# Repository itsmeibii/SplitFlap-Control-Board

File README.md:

# SplitFlap Display Control Board

A Raspberry Pi 4 controller board for a split-flap display with HUB75 LED matrix panels. One USB-C PD cable powers the Pi, the split-flap motor drivers and the LED panels.

## Features
- **USB-C PD input:** an Adafruit HUSB238 breakout asks the charger for 20 V / 3 A (60 W)
- **12–20 V → 5 V buck converter:** TI TPS56A37, up to ~8 A. An EN/UVLO divider keeps it off until PD has negotiated, and its power-good goes to a Pi GPIO.
- **Pi protection:** a TPS259474 eFuse on the Pi's 5 V rail (5.83 V overvoltage cutoff, 3.5 A current limit, power-good to a GPIO)
- **Fused outputs:** 7.5 A for the HUB75 panels and 3 A for the split-flap modules (ATO blade fuses)
- **TVS protection:** SMAJ22A on VBUS and SMAJ6.0A on 5 V
- **Connectors:** HUB75 data header, split-flap (Chainlink) data bus, two config buttons and status LEDs

## Repo layout
| Path | Contents |
|---|---|
| `control board/ControlBoard/` | KiCad 10 project (schematic, PCB, custom symbols/footprints) |
| `control board/ControlBoard/fab/` | JLCPCB gerbers, assembly files, DigiKey BOM |
| `housing/` | Enclosure: CadQuery scripts, STEP and STL files |
| `pi/` | Raspberry Pi smoke test for the Chainlink driver |
| `hub_75_test/` | HUB75 LED panel test firmware (Arduino + ESP-IDF) |
| `docs/` | Schematic PDF and renders |

## Schematics

## PCB
| Top | Bottom |
|:---:|:---:|
|  |  |

## Enclosure

The split-flap mechanism and driver boards come from [scottbez1/splitflap](https://github.com/scottbez1/splitflap). This repo contains only the control board and enclosure I designed for it.

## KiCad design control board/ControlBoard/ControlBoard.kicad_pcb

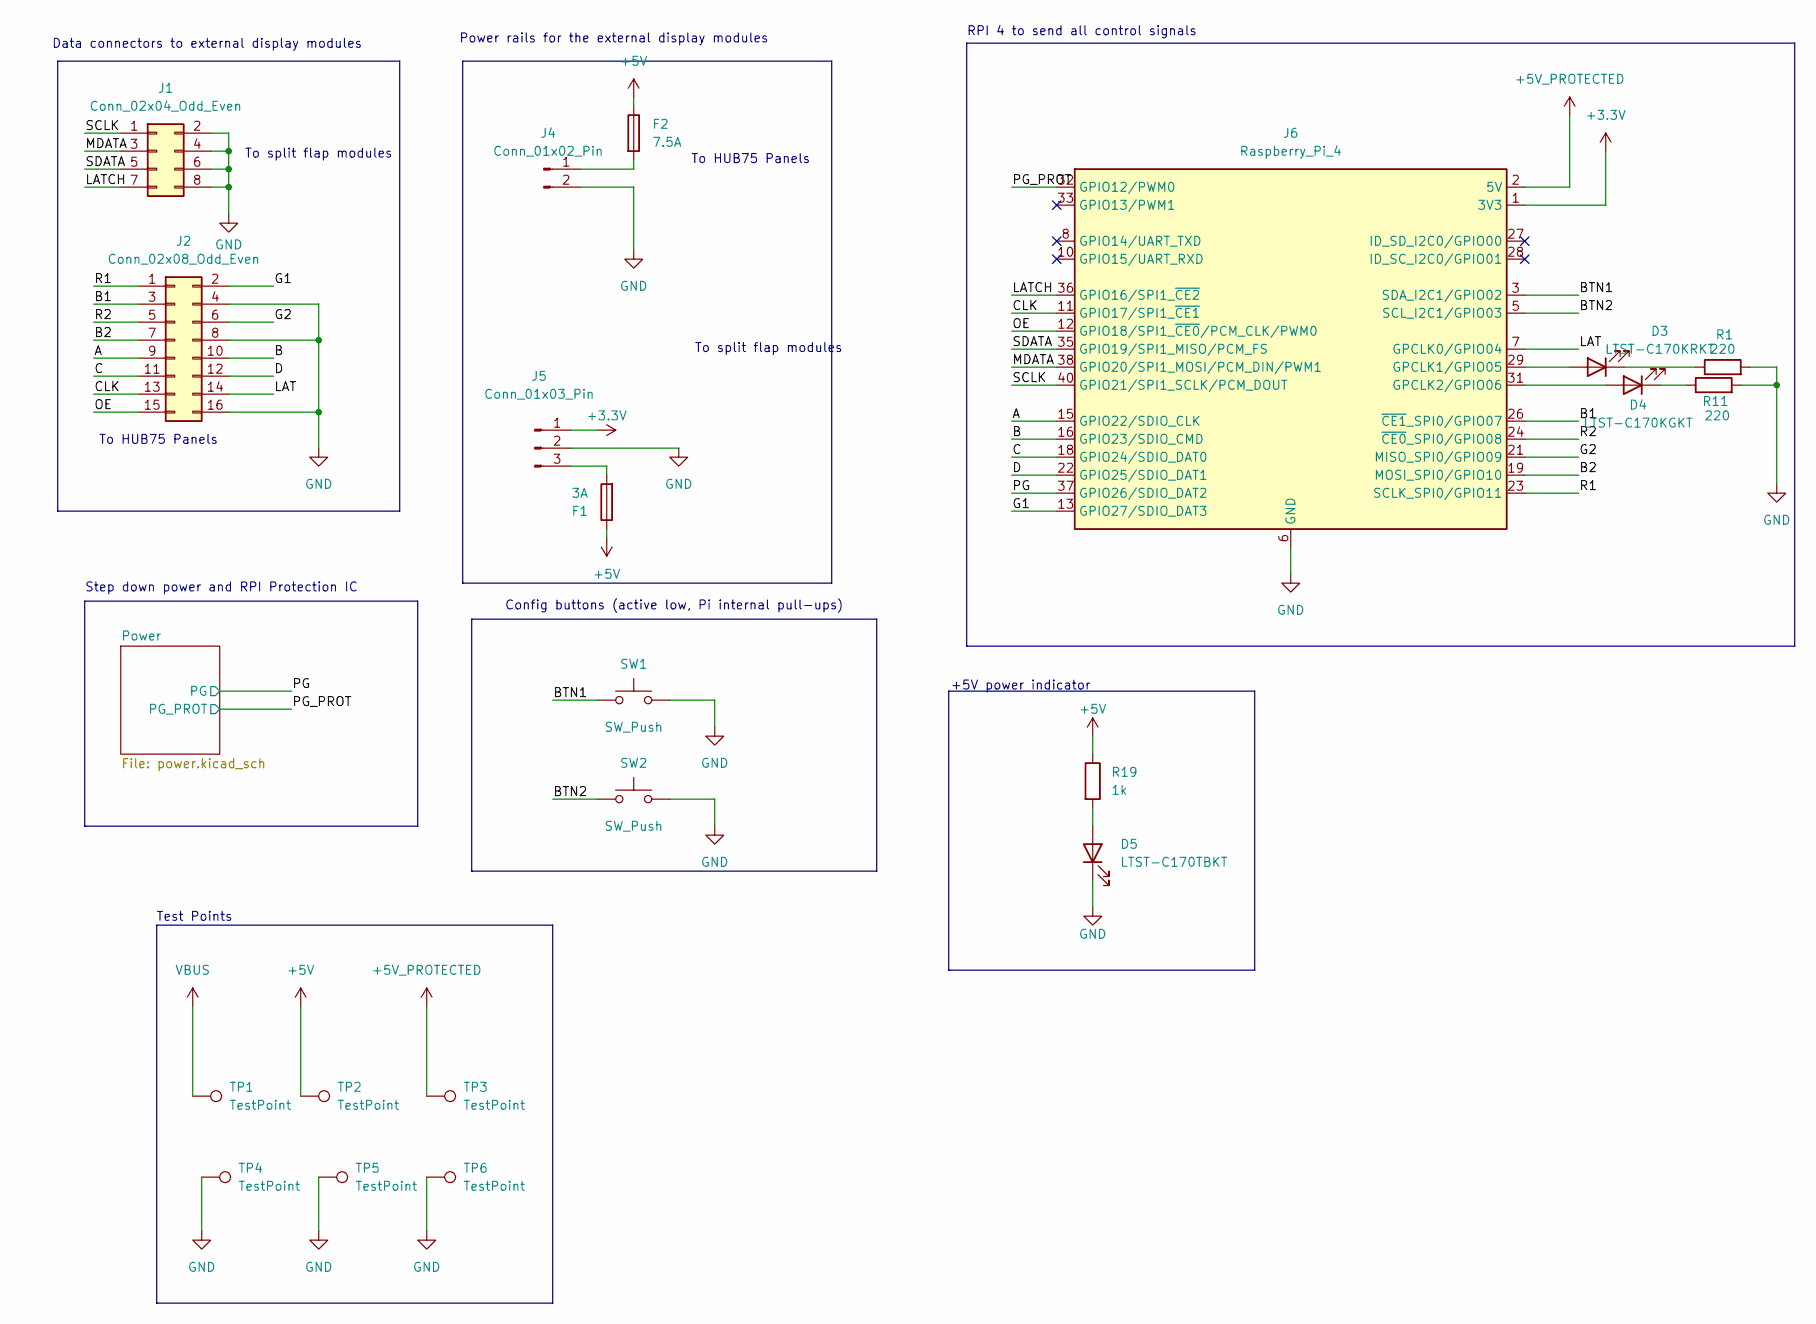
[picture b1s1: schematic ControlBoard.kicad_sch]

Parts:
D3: LTST-C170KRKT; LED_0805_2012Metric_Pad1.15x1.40mm_HandSolder; DigiKey Part # 160-1415-1-ND
D4: LTST-C170KGKT; LED_0805_2012Metric_Pad1.15x1.40mm_HandSolder; DigiKey Part # 160-1414-1-ND
D5: LTST-C170TBKT; LED_0805_2012Metric_Pad1.15x1.40mm_HandSolder; DigiKey Part # 160-1579-1-ND
F1: 3A; Fuseholder_Blade_Mini_Keystone_3568; MPN 3568; DigiKey Part # 36-3568-ND
F2: 7.5A; Fuseholder_Blade_Mini_Keystone_3568; MPN 3568; DigiKey Part # 36-3568-ND
J1: Conn_02x04_Odd_Even; IDC-Header_2x04_P2.54mm_Vertical; DigiKey Part # 732-5395-ND
J2: Conn_02x08_Odd_Even; IDC-Header_2x08_P2.54mm_Vertical; DigiKey Part # 732-2095-ND
J4: Conn_01x02_Pin; TerminalBlock_CUI_TB007-508-02_1x02_P5.08mm_Horizontal; DigiKey Part # 102-6191-ND
J5: Conn_01x03_Pin; TerminalBlock_CUI_TB007-508-03_1x03_P5.08mm_Horizontal; DigiKey Part # 102-6204-ND
J6: Raspberry_Pi_4; PinSocket_2x20_P2.54mm_Vertical; DigiKey Part # 2223-SSK04-FPH-254-B20-ND
R1, R11: 220; R_0805_2012Metric; DigiKey Part # 311-220CRCT-ND
R19: 1k; R_0805_2012Metric; DigiKey Part # 311-1.00KCRCT-ND
SW1, SW2: SW_Push; SW_PUSH_6mm; DigiKey Part # SW400-ND
TP1, TP2, TP3, TP4, TP5, TP6: TestPoint; TestPoint_Pad_D1.0mm

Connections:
+3.3V: J5.1, J6.1 (3V3), J6.17 (3V3); also elsewhere on the board
+5V: F1.1, F2.1, R19.1, TP2.1 (1_1); also elsewhere on the board
+5V_PROTECTED: J6.2 (5V), J6.4 (5V), TP3.1 (1_1); also elsewhere on the board
/A: J2.9, J6.15 (GPIO22/SDIO_CLK)
/B: J2.10, J6.16 (GPIO23/SDIO_CMD)
/B1: J2.3, J6.26 (~CE1_SPI0/GPIO07)
/B2: J2.7, J6.19 (MOSI_SPI0/GPIO10)
/BTN1: J6.3 (SDA_I2C1/GPIO02), SW1.1
/BTN2: J6.5 (SCL_I2C1/GPIO03), SW2.1
/C: J2.11, J6.18 (GPIO24/SDIO_DAT0)
/CLK: J2.13, J6.11 (GPIO17/SPI1_~CE1)
/D: J2.12, J6.22 (GPIO25/SDIO_DAT1)
/G1: J2.2, J6.13 (GPIO27/SDIO_DAT3)
/G2: J2.6, J6.21 (MISO_SPI0/GPIO09)
/LAT: J2.14, J6.7 (GPCLK0/GPIO04)
/LATCH: J1.7, J6.36 (GPIO16/SPI1_~CE2)
/MDATA: J1.3, J6.38 (GPIO20/SPI1_MOSI/PCM_DIN/PWM1)
/OE: J2.15, J6.12 (GPIO18/SPI1_~CE0/PCM_CLK/PWM0)
/PG: J6.37 (GPIO26/SDIO_DAT2); also elsewhere on the board
/PG_PROT: J6.32 (GPIO12/PWM0); also elsewhere on the board
/R1: J2.1, J6.23 (SCLK_SPI0/GPIO11)
/R2: J2.5, J6.24 (~CE0_SPI0/GPIO08)
/SCLK: J1.1, J6.40 (GPIO21/SPI1_SCLK/PCM_DOUT)
/SDATA: J1.5, J6.35 (GPIO19/SPI1_MISO/PCM_FS)
GND: D5.1 (K), J1.2, J1.4, J1.6, J1.8, J2.4, J2.8, J2.16, J4.2, J5.2, J6.6 (GND), J6.9 (GND), J6.14 (GND), J6.20 (GND), J6.25 (GND), J6.30 (GND), J6.34 (GND), J6.39 (GND), R1.2, R11.2, SW1.2, SW2.2, TP4.1 (1_1), TP5.1 (1_1), TP6.1 (1_1); also elsewhere on the board
unnamed: D3.2 (A), J6.29 (GPCLK1/GPIO05)
unnamed: D3.1 (K), R1.1
unnamed: D4.2 (A), J6.31 (GPCLK2/GPIO06)
unnamed: D4.1 (K), R11.1
unnamed: D5.2 (A), R19.2
unnamed: F2.2, J4.1
unnamed: F1.2, J5.3
VBUS: TP1.1 (1_1); also elsewhere on the board

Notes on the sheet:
+5V power indicator
RPI 4 to send all control signals
To split flap modules
Power rails for the external display modules
Step down power and RPI Protection IC
Config buttons (active low, Pi internal pull-ups)
Data connectors to external display modules
To HUB75 Panels
Test Points

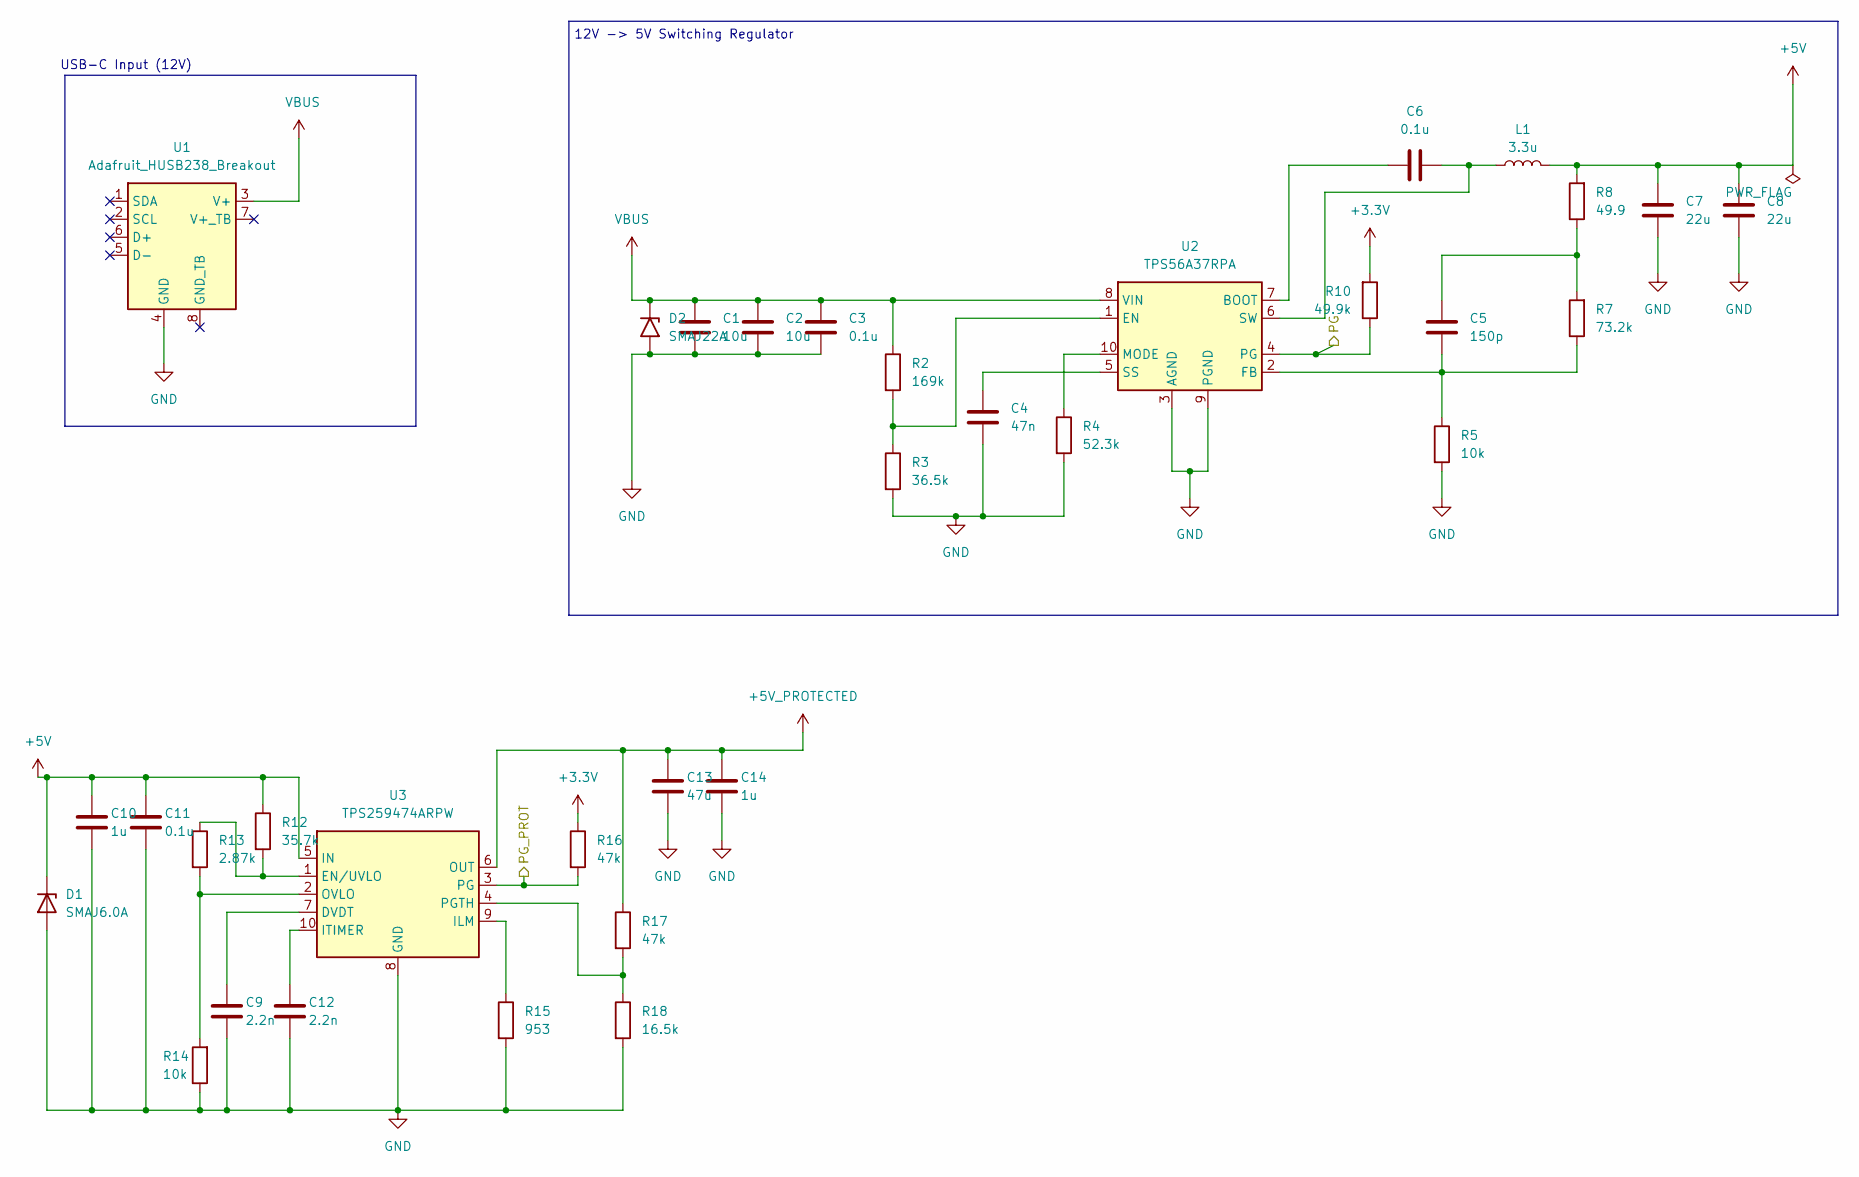
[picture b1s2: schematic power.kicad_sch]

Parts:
C1, C2: 10u; C_1206_3216Metric; DigiKey Part # 4713-GMC31X7R106K50NTCT-ND
C3, C6, C11: 0.1u; C_0805_2012Metric; DigiKey Part # 1276-1003-1-ND
C4: 47n; C_0805_2012Metric; DigiKey Part # 399-C0805C473K5RACTUCT-ND
C5: 150p; C_0805_2012Metric; DigiKey Part # 399-C0805C151J5GACTUCT-ND
C7, C8: 22u; C_1210_3225Metric; DigiKey Part # 490-3889-1-ND
C9, C12: 2.2n; C_0805_2012Metric; DigiKey Part # 1276-2993-1-ND
C10, C14: 1u; C_0805_2012Metric; DigiKey Part # 399-C0805C105K3RACTUCT-ND
C13: 47u; C_1210_3225Metric; DigiKey Part # 587-5479-1-ND
D1: SMAJ6.0A; D_SMA; DigiKey Part # SMAJ6.0ALFCT-ND
D2: SMAJ22A; D_SMA; DigiKey Part # SMAJ22ABCT-ND
L1: 3.3u; L_Wuerth_HCI-1050; DigiKey Part # 732-1169-1-ND
R2: 169k; R_0805_2012Metric; DigiKey Part # RMCF0805FT169KCT-ND
R3: 36.5k; R_0805_2012Metric; DigiKey Part # 311-36.5KCRCT-ND
R4: 52.3k; R_0805_2012Metric; DigiKey Part # 311-52.3KCRCT-ND
R5, R14: 10k; R_0805_2012Metric; DigiKey Part # 311-10.0KCRCT-ND
R7: 73.2k; R_0805_2012Metric; DigiKey Part # 311-73.2KCRCT-ND
R8: 49.9; R_0805_2012Metric; DigiKey Part # 311-49.9CRCT-ND
R10: 49.9k; R_0805_2012Metric; DigiKey Part # 311-49.9KCRCT-ND
R12: 35.7k; R_0805_2012Metric; DigiKey Part # 311-35.7KCRCT-ND
R13: 2.87k; R_0805_2012Metric; DigiKey Part # 311-2.87KCRCT-ND
R15: 953; R_0805_2012Metric; DigiKey Part # 311-953CRCT-ND
R16, R17: 47k; R_0805_2012Metric; DigiKey Part # 311-47.0KCRCT-ND
R18: 16.5k; R_0805_2012Metric; DigiKey Part # 311-16.5KCRCT-ND
U1: Adafruit_HUSB238_Breakout; DigiKey 1528-5807-ND
U2: TPS56A37RPA; Texas_RPA0010A_VQFN-HR-10_3x3mm_P0.5mm; DigiKey Part # 296-TPS56A37RPARCT-ND
U3: TPS259474ARPW; Texas_RPW0010A_VQFN-HR-10_2x2mm_P0.475mm; DigiKey Part # 296-TPS259474ARPWRCT-ND

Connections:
+3.3V: R10.2, R16.1; also elsewhere on the board
+5V: C7.2, C8.2, C10.1, C11.1, D1.1 (K), L1.2, R8.2, R12.1, U3.5 (IN); also elsewhere on the board
+5V_PROTECTED: C13.1, C14.1, R17.1, U3.6 (OUT); also elsewhere on the board
/PG: R10.1, U2.4 (PG); also elsewhere on the board
/PG_PROT: R16.2, U3.3 (PG); also elsewhere on the board
GND: C1.2, C2.2, C3.2, C4.2, C7.1, C8.1, C9.2, C10.2, C11.2, C12.2, C13.2, C14.2, D1.2 (A), D2.2 (A2), R3.2, R4.2, R5.2, R14.1, R15.2, R18.2, U1.4 (GND), U2.3 (AGND), U2.9 (PGND), U3.8 (GND); also elsewhere on the board
unnamed: C5.1, R7.2, R8.1
unnamed: C6.1, U2.7 (BOOT)
unnamed: R2.2, R3.1, U2.1 (EN)
unnamed: C5.2, R5.1, R7.1, U2.2 (FB)
unnamed: R4.1, U2.10 (MODE)
unnamed: C4.1, U2.5 (SS)
unnamed: C6.2, L1.1, U2.6 (SW)
unnamed: C9.1, U3.7 (DVDT)
unnamed: R12.2, R13.1, U3.1 (EN/UVLO)
unnamed: R15.1, U3.9 (ILM)
unnamed: C12.1, U3.10 (ITIMER)
unnamed: R13.2, R14.2, U3.2 (OVLO)
unnamed: R17.2, R18.1, U3.4 (PGTH)
VBUS: C1.1, C2.1, C3.1, D2.1 (A1), R2.1, U1.3 (V+), U2.8 (VIN); also elsewhere on the board

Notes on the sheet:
USB-C Input (12V)
12V -> 5V Switching Regulator

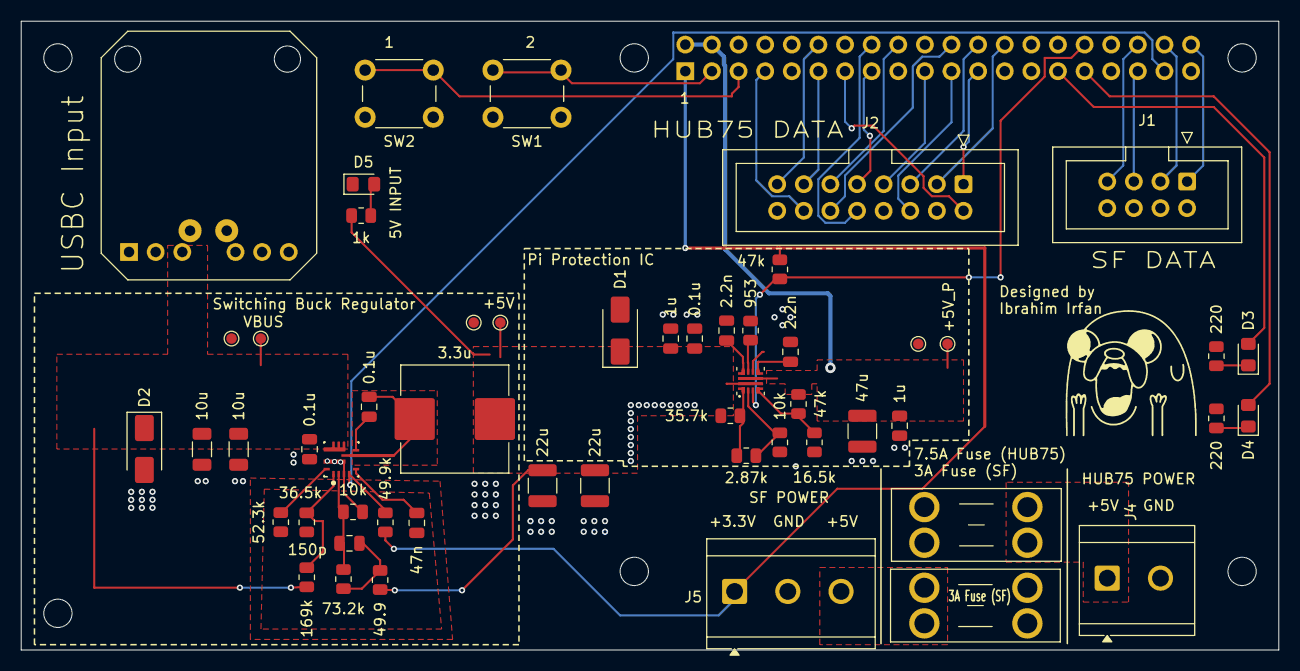
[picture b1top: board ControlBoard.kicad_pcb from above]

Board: 2 copper layers, 120.0 x 60.0 mm, 62 parts (1 on the bottom side), 46 nets.

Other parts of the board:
H1, H2, H3, H4, H5, H6: MountingHole_2.7mm_M2.5
LOGO1: Logo_Jake; Logo_Jake_Silkscreen_12mm

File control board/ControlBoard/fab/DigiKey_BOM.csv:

Qty per board,References,Value,Footprint,DigiKey Part #,Who solders
2,C1 C2,10u,C_1206_3216Metric,4713-GMC31X7R106K50NTCT-ND,You
3,C3 C6 C11,0.1u,C_0805_2012Metric,1276-1003-1-ND,You
1,C4,47n,C_0805_2012Metric,399-C0805C473K5RACTUCT-ND,You
1,C5,150p,C_0805_2012Metric,399-C0805C151J5GACTUCT-ND,You
2,C7 C8,22u,C_1210_3225Metric,490-3889-1-ND,You
2,C9 C12,2.2n,C_0805_2012Metric,1276-2993-1-ND,You
2,C10 C14,1u,C_0805_2012Metric,399-C0805C105K3RACTUCT-ND,You
1,C13,47u,C_1210_3225Metric,587-5479-1-ND,You
1,D1,SMAJ6.0A,D_SMA,SMAJ6.0ALFCT-ND,You
1,D2,SMAJ22A,D_SMA,SMAJ22ABCT-ND,You
1,D3,LTST-C170KRKT,LED_0805_2012Metric_Pad1.15x1.40mm_HandSolder,160-1415-1-ND,You
1,D4,LTST-C170KGKT,LED_0805_2012Metric_Pad1.15x1.40mm_HandSolder,160-1414-1-ND,You
1,D5,LTST-C170TBKT,LED_0805_2012Metric_Pad1.15x1.40mm_HandSolder,160-1579-1-ND,You
1,F1,3A,Fuseholder_Blade_Mini_Keystone_3568,36-3568-ND,You
1,F2,7.5A,Fuseholder_Blade_Mini_Keystone_3568,36-3568-ND,You
1,J1,Conn_02x04_Odd_Even,IDC-Header_2x04_P2.54mm_Vertical,732-5395-ND,You
1,J2,Conn_02x08_Odd_Even,IDC-Header_2x08_P2.54mm_Vertical,732-2095-ND,You
1,J4,Conn_01x02_Pin,TerminalBlock_CUI_TB007-508-02_1x02_P5.08mm_Horizontal,102-6203-ND,You
1,J5,Conn_01x03_Pin,TerminalBlock_CUI_TB007-508-03_1x03_P5.08mm_Horizontal,102-6204-ND,You
1,J6,Raspberry_Pi_4,PinSocket_2x20_P2.54mm_Vertical,2223-SSK04-FPH-254-B20-ND,You
1,L1,3.3u,L_Wuerth_HCI-1050,732-1169-1-ND,You
2,R1 R11,220,R_0805_2012Metric,311-220CRCT-ND,You
1,R2,169k,R_0805_2012Metric,RMCF0805FT169KCT-ND,You
1,R3,36.5k,R_0805_2012Metric,311-36.5KCRCT-ND,You
1,R4,52.3k,R_0805_2012Metric,311-52.3KCRCT-ND,You
2,R5 R14,10k,R_0805_2012Metric,311-10.0KCRCT-ND,You
1,R7,73.2k,R_0805_2012Metric,311-73.2KCRCT-ND,You
1,R8,49.9,R_0805_2012Metric,311-49.9CRCT-ND,You
1,R10,49.9k,R_0805_2012Metric,311-49.9KCRCT-ND,You
1,R12,35.7k,R_0805_2012Metric,311-35.7KCRCT-ND,You
1,R13,2.87k,R_0805_2012Metric,311-2.87KCRCT-ND,You
1,R15,953,R_0805_2012Metric,311-953CRCT-ND,You
2,R16 R17,47k,R_0805_2012Metric,311-47.0KCRCT-ND,You
1,R18,16.5k,R_0805_2012Metric,311-16.5KCRCT-ND,You
1,R19,1k,R_0805_2012Metric,311-1.00KCRCT-ND,You
2,SW1 SW2,SW_Push,SW_PUSH_6mm,SW400-ND,You
1,U1,Adafruit_HUSB238_Breakout,Adafruit_HUSB238_Breakout,1528-5807-ND,You
1,U2,TPS56A37RPA,Texas_RPA0010A_VQFN-HR-10_3x3mm_P0.5mm,296-TPS56A37RPARCT-ND,JLC (Global Sourcing - do not order)
1,U3,TPS259474ARPW,Texas_RPW0010A_VQFN-HR-10_2x2mm_P0.475mm,296-TPS259474ARPWRCT-ND,JLC (Global Sourcing - do not order)
6,"TP1,TP2,TP3,TP4,TP5,TP6",TestPoint,TestPoint_Pad_D1.0mm,(none - bare copper pad),Nothing to buy or solder

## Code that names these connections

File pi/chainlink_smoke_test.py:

#!/usr/bin/env python3
"""
Chainlink Driver smoke test for a Raspberry Pi 4 -- steps all six modules at once
so the peak motor-supply current can be measured.

Wiring (Chainlink "Input" 2x4 header -> Pi, BCM numbering):
    1 CLOCK      -> GPIO21 (pin 40)
    3 MOTOR      -> GPIO20 (pin 38)
    5 SENSOR_OUT -> GPIO19 (pin 35)
    7 LATCH      -> GPIO16 (pin 36)
    even pins    -> GND
    "Logic 3.3-5V" terminal -> Pi 3V3 (pin 1/17)   -- NOT 5V
    "Motor" terminal        -> bench supply V+, supply GND shared with the Pi

The bit layout mirrors firmware/src/spi_io_config.h (CHAINLINK, NUM_MODULES=6):
4 bytes are shifted out MSB-first, byte 0 first, so byte 3 lands in the
74HC595 nearest the input header. One LATCH line drives both the 595 RCLK
(rising edge = outputs update) and the 74HC165 SH/LD (low = parallel load,
high = shift), so after latching high we clock in one sensor byte.

Usage (needs python3-lgpio, preinstalled on Raspberry Pi OS Bookworm):
    python3 chainlink_smoke_test.py                 # step all 6 for 10 s
    python3 chainlink_smoke_test.py -t 30 -p 1800   # 30 s at 1.8 ms/step
    python3 chainlink_smoke_test.py --hold 5        # hold coils on 5 s (static worst case)
    python3 chainlink_smoke_test.py --modules 0 3   # only modules A and D
"""

import argparse
import signal
import sys
import time

import lgpio

PIN_CLK = 21
PIN_DATA = 20
PIN_SENSOR = 19
PIN_LATCH = 16

NUM_MODULES = 6
MOTOR_BYTES = 4

# (byte index, bit shift) of each module's 4 coil bits -- from initialize_modules()
MOTOR_SLOT = [(3, 0), (3, 4), (2, 0), (1, 4), (0, 0), (0, 4)]
# (byte index, bit mask) of each module's LED -- from chainlink_set_led()
LED_SLOT = [(2, 1 << 4), (2, 1 << 5), (2, 1 << 6), (1, 1 << 0), (1, 1 << 1), (1, 1 << 2)]

# Two-phase-on full stepping, same as the firmware (two coils energized per step)
STEP_PATTERN = [0b1100, 0b0110, 0b0011, 0b1001]

# Firmware starts at 10 ms/step and accelerates to ~1.6 ms/step
START_PERIOD_US = 10000
RAMP_STEPS = 72


class Chainlink:
    def __init__(self):
        self.h = lgpio.gpiochip_open(0)
        for pin in (PIN_CLK, PIN_DATA, PIN_LATCH):
            lgpio.gpio_claim_output(self.h, pin, 0)
        lgpio.gpio_claim_input(self.h, PIN_SENSOR)

    def io(self, motor_bytes):
        """Shift out motor bytes, latch them, and read back one sensor byte."""
        h = self.h
        write = lgpio.gpio_write
        write(h, PIN_LATCH, 0)
        for byte in motor_bytes:
            for bit in range(7, -1, -1):
                write(h, PIN_DATA, (byte >> bit) & 1)
                write(h, PIN_CLK, 1)
                write(h, PIN_CLK, 0)
        # Rising edge: 595 outputs update, 165 freezes its inputs for shifting
        write(h, PIN_LATCH, 1)
        sensors = 0
        for _ in range(8):
            sensors = (sensors << 1) | lgpio.gpio_read(h, PIN_SENSOR)
            write(h, PIN_CLK, 1)
            write(h, PIN_CLK, 0)
        return sensors

    def all_off(self):
        self.io([0] * MOTOR_BYTES)

    def close(self):
        try:
            self.all_off()
        finally:
            lgpio.gpiochip_close(self.h)


def build_frame(modules, phase, leds=0):
    buf = [0] * MOTOR_BYTES
    for m in modules:
        idx, shift = MOTOR_SLOT[m]
        buf[idx] |= STEP_PATTERN[phase] << shift
    for m in range(NUM_MODULES):
        if leds & (1 << m):
            idx, mask = LED_SLOT[m]
            buf[idx] |= mask
    return buf


def wait_until(deadline_ns):
    while time.perf_counter_ns() < deadline_ns:
        pass


def run_stepping(link, modules, seconds, period_us):
    print(f"Stepping modules {[chr(65 + m) for m in modules]} for {seconds:.1f} s "
          f"at {period_us} us/step (~{60e6 / (period_us * 2048):.1f} RPM)")
    phase = 0
    leds = 0
    last_home = 0
    home_hits = [0] * NUM_MODULES
    overruns = 0
    worst_io_us = 0
    steps = 0

    start = time.perf_counter_ns()
    end = start + int(seconds * 1e9)
    deadline = start
    while deadline < end:
        # Linear ramp from START_PERIOD_US down to the target period
        if steps < RAMP_STEPS:
            p = START_PERIOD_US + (period_us - START_PERIOD_US) * steps // RAMP_STEPS
        else:
            p = period_us
        deadline += p * 1000

        t0 = time.perf_counter_ns()
        sensors = link.io(build_frame(modules, phase, leds))
        worst_io_us = max(worst_io_us, (time.perf_counter_ns() - t0) // 1000)

        # Home sensor bit set = flap at home; light the module's LED and count rising edges
        home = sensors & 0x3F
        for m in range(NUM_MODULES):
            if home & ~last_home & (1 << m):
                home_hits[m] += 1
        last_home = home
        leds = home

        phase = (phase + 1) % 4
        steps += 1
        if time.perf_counter_ns() > deadline:
            overruns += 1
        wait_until(deadline)

    link.all_off()
    revs = steps / 2048
    print(f"Done: {steps} steps (~{revs:.2f} rev), worst shift-register IO {worst_io_us} us, "
          f"{overruns} late steps")
    print("Home sensor hits per module (expect ~1 per revolution on connected modules):")
    print("  " + "  ".join(f"{chr(65 + m)}={home_hits[m]}" for m in range(NUM_MODULES)))


def run_hold(link, modules, seconds):
    print(f"Holding phase AB on modules {[chr(65 + m) for m in modules]} for {seconds:.1f} s "
          "(static worst-case current)")
    link.io(build_frame(modules, 0))
    time.sleep(seconds)
    link.all_off()
    print("Coils off.")


def main():
    ap = argparse.ArgumentParser(description=__doc__, formatter_class=argparse.RawDescriptionHelpFormatter)
    ap.add_argument("-t", "--time", type=float, default=10.0, help="seconds to step (default 10)")
    ap.add_argument("-p", "--period", type=int, default=2000,
                    help="microseconds per step after ramp-up (default 2000; firmware max speed is ~1600)")
    ap.add_argument("--hold", type=float, metavar="SECONDS",
                    help="instead of stepping, hold coils energized this long (max 10)")
    ap.add_argument("--modules", type=int, nargs="+", default=list(range(NUM_MODULES)),
                    choices=range(NUM_MODULES), metavar="N", help="module indices 0-5 (A-F), default all")
    ap.add_argument("-y", "--yes", action="store_true", help="skip the 'turn on motor power' prompt")
    args = ap.parse_args()

    if args.period < 1000:
        ap.error("period below 1000 us will just stall a 28BYJ-48")
    if args.hold is not None and not 0 < args.hold <= 10:
        ap.error("--hold must be between 0 and 10 seconds")

    link = Chainlink()

    def bail(signum, frame):
        raise KeyboardInterrupt
    signal.signal(signal.SIGTERM, bail)

    try:
        link.all_off()
        link.all_off()
        print("Shift registers cleared (all coils off).")
        if not args.yes:
            input("Turn on motor power now, then press Enter... ")
        if args.hold is not None:
            run_hold(link, args.modules, args.hold)
        else:
            run_stepping(link, args.modules, args.time, args.period)
    except KeyboardInterrupt:
        print("\nInterrupted.")
    finally:
        link.close()
        print("All coils off. Safe to cut motor power.")


if __name__ == "__main__":
    sys.exit(main())
